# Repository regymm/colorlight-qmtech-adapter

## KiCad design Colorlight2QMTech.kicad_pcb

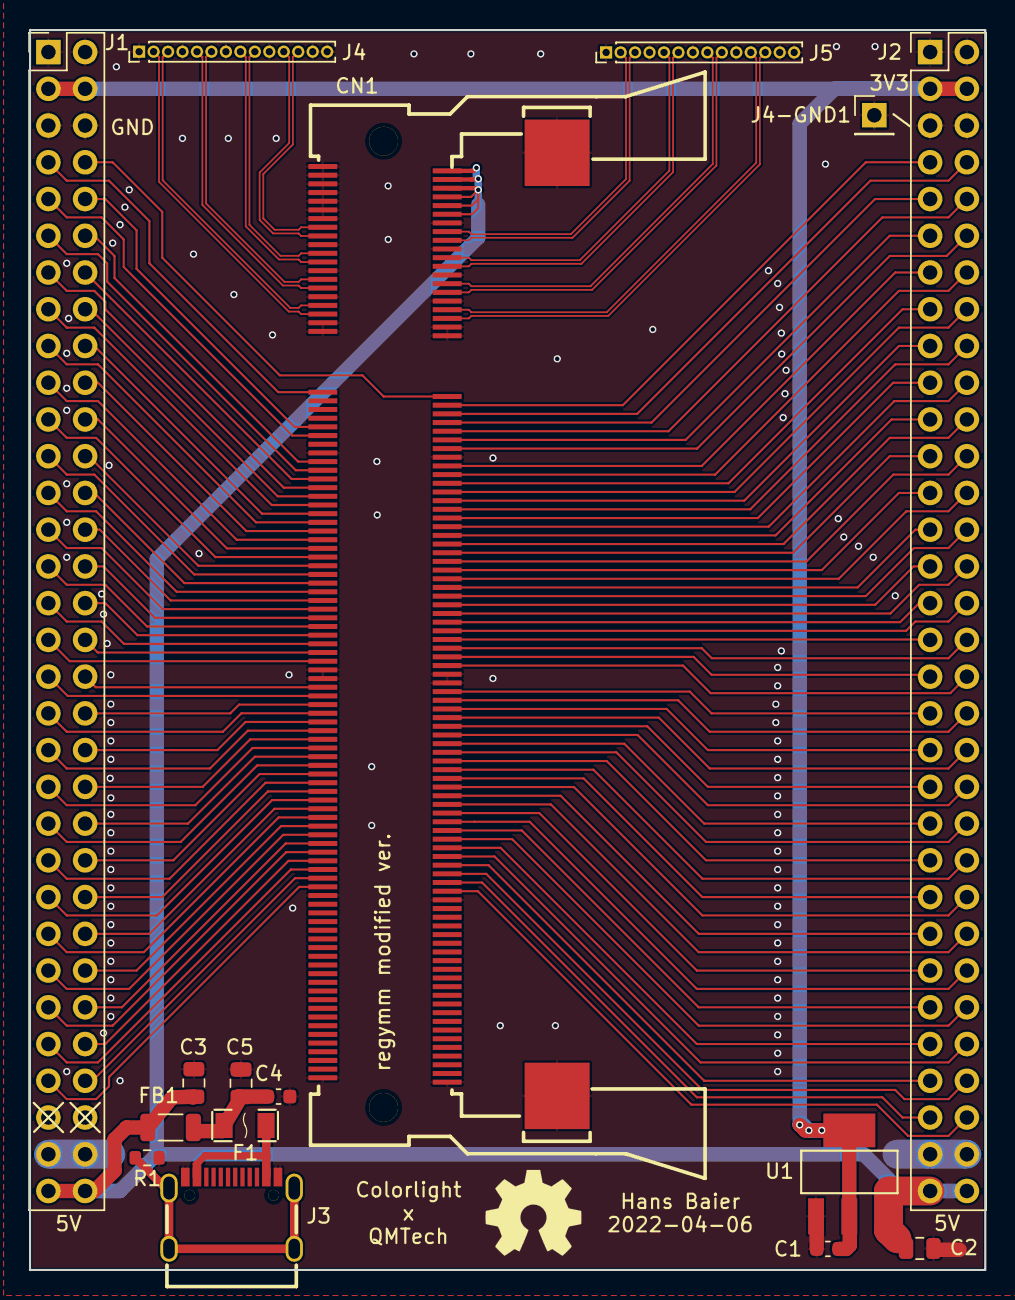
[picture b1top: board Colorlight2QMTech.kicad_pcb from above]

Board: 2 copper layers, 66.0 x 85.7 mm, 17 parts (0 on the bottom side), 128 nets.

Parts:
C1, C4: 100n; C_0603_1608Metric
C2, C5: 10u; C_0805_2012Metric
C3: 10n; C_0805_2012Metric
CN1: 1473005-4; SO-DIMM-SMD_200P-P0.60_1473005-4
F1: JK-NSMD050-30V; F1206
FB1: 2A; L_1206_3216Metric
J1, J2: Conn_02x32_Odd_Even; PinHeader_2x32_P2.54mm_Vertical
J3: Connector_USB_C_Receptacle_USB2.0; USB-C_SMD-TYPE-C-31-M-12
J4, J5: Conn_01x14_Male; PinHeader_1x14_P1.00mm_Vertical
J4-GND1: Conn_01x01_Male; PinHeader_1x01_P2.54mm_Vertical
N1: OHWLOGO; OSHW-Symbol_6.7x6mm_SilkScreen
R1: 1M; R_0603_1608Metric
U1: AMS1117-3.3; SOT-223-3_L6.5-W3.4-P2.30-LS7.0-BR

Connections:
+3V3: C1.2, J1.3, J1.4, J2.3, J2.4, U1.2 (Vout), U1.4 (Vout)
+5V: C2.2, C3.2, CN1.2, CN1.4, CN1.6, CN1.8, CN1.10, CN1.12, FB1.1, J1.63, J1.64, J2.63, J2.64, U1.3 (Vin)
/5V_FILTER: C4.2, C5.2, F1.1, FB1.2
/A2: CN1.154, J2.59
/A3: CN1.139, J1.49
/A18: CN1.127, J1.43
/A19: CN1.123, J1.41
/B1: CN1.143, J1.51
/B2: CN1.156, J2.60
/B3: CN1.152, J2.58
/B4: CN1.133, J1.48
/B18: CN1.121, J1.42
/B19: CN1.119, J1.39
/B20: CN1.117, J1.40
/C1: CN1.145, J1.54
/C2: CN1.141, J1.52
/C3: CN1.135, J1.47
/C4: CN1.131, J1.45
/C17: CN1.125, J1.44
/C18: CN1.51, J1.9
/C20: CN1.115, J1.37
/D1: CN1.149, J1.56
/D2: CN1.147, J1.53
/D3: CN1.129, J1.46
/D16: CN1.118, J2.41
/D17: CN1.114, J2.39
/D18: CN1.112, J2.38
/D19: CN1.113, J1.38
/D20: CN1.111, J1.35
/E1: CN1.153, J1.58
/E2: CN1.151, J1.55
/E3: CN1.137, J1.50
/E4: CN1.128, J2.46
/E5: CN1.124, J2.44
/E6: CN1.122, J2.43
/E16: CN1.104, J2.36
/E17: CN1.110, J2.37
/E18: CN1.98, J2.33
/E19: CN1.109, J1.36
/E20: CN1.103, J1.33
/F1: CN1.130, J2.47
/F2: CN1.155, J1.57
/F3: CN1.132, J2.48
/F4: CN1.126, J2.45
/F5: CN1.120, J2.42
/F16: CN1.102, J2.35
/F17: CN1.100, J2.34
/F18: CN1.94, J2.31
/F19: CN1.101, J1.34
/F20: CN1.99, J1.31
/G3: CN1.134, J2.49
/G5: CN1.116, J2.40
/G16: CN1.96, J2.32
/G18: CN1.90, J2.29
/G19: CN1.97, J1.32
/G20: CN1.95, J1.29
/H3: CN1.136, J2.50
/H4: CN1.138, J2.51
/H5: CN1.140, J2.52
/H16: CN1.92, J2.30
/H17: CN1.88, J2.28
/H18: CN1.86, J2.27
/H20: CN1.93, J1.30
/J4: CN1.142, J2.53
/J5: CN1.144, J2.54
/J16: CN1.80, J2.24
/J17: CN1.84, J2.26
/J18: CN1.82, J2.25
/J19: CN1.91, J1.27
/J20: CN1.89, J1.28
/K3: CN1.146, J2.55
/K4: CN1.148, J2.56
/K5: CN1.150, J2.57
/K18: CN1.49, J1.10
/K19: CN1.87, J1.25
/K20: CN1.85, J1.26
/L4: CN1.74, J2.21
/L5: CN1.76, J2.22
/L18: CN1.83, J1.23
/L20: CN1.81, J1.24
/M1: CN1.54, J2.12
/M3: CN1.64, J2.16
/M4: CN1.72, J2.20
/M17: CN1.65, J1.16
/M18: CN1.79, J1.21
/N2: CN1.58, J2.13
/N3: CN1.60, J2.14
/N4: CN1.70, J2.19
/N17: CN1.75, J1.19
/N18: CN1.77, J1.22
/P16: CN1.78, J2.23
/P17: CN1.63, J1.13
/P18: CN1.73, J1.20
/R1: CN1.42, J1.8
/R3: CN1.68, J2.18
/R17: CN1.61, J1.14
/R18: CN1.59, J1.11
/T1: CN1.44, J2.7
/T2: CN1.62, J2.15
/T3: CN1.66, J2.17
/T17: CN1.67, J1.15
/T18: CN1.57, J1.12
/U1: CN1.46, J2.8
/U16: CN1.41, J1.7
/U17: CN1.71, J1.17
/U18: CN1.69, J1.18
/V1: CN1.52, J2.11
/W1: CN1.50, J2.10
/Y2: CN1.48, J2.9
/eth1_1+: CN1.15, J4.12
/eth1_1-: CN1.17, J4.11
/eth1_2+: CN1.23, J4.8
/eth1_2-: CN1.21, J4.9
/eth1_3+: CN1.27, J4.6
/eth1_3-: CN1.29, J4.5
/eth1_4+: CN1.35, J4.2
/eth1_4-: CN1.33, J4.3
/eth2_1+: CN1.16, J5.2
/eth2_1-: CN1.18, J5.3
/eth2_2+: CN1.24, J5.6
/eth2_2-: CN1.22, J5.5
/eth2_3+: CN1.28, J5.8
/eth2_3-: CN1.30, J5.9
/eth2_4+: CN1.36, J5.12
/eth2_4-: CN1.34, J5.11
GND: C1.1, C2.1, C3.1, C4.1, C5.1, CN1.1, CN1.3, CN1.5, CN1.7, CN1.9, CN1.11, CN1.13, CN1.14, CN1.19, CN1.20, CN1.25, CN1.26, CN1.31, CN1.32, CN1.37, CN1.38, CN1.39, CN1.40, CN1.55, CN1.56, CN1.105, CN1.106, CN1.107, CN1.108, CN1.157, CN1.158, CN1.199, CN1.200, CN1.201, J1.1, J1.2, J1.5, J1.6, J1.61, J1.62, J2.1, J2.2, J2.5, J2.6, J2.61, J2.62, J3.A1 (GND), J3.A12 (GND), J3.B1 (GND), J3.B12 (GND), J4.1, J4.4, J4.7, J4.10, J4.13, J4.14, J4-GND1.1, J5.1, J5.4, J5.7, J5.10, J5.13, J5.14, R1.1, U1.1 (GND/ADJ)
unnamed: F1.2, J3.A4 (VBUS), J3.A9 (VBUS), J3.B4 (VBUS), J3.B9 (VBUS)
unnamed: J3.S1 (SHIELD), R1.2

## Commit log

2022-08-25 regymm modified 2 layer ver.
